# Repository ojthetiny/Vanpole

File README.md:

# Vanpole
tadpole, but van

Layout support

Pic

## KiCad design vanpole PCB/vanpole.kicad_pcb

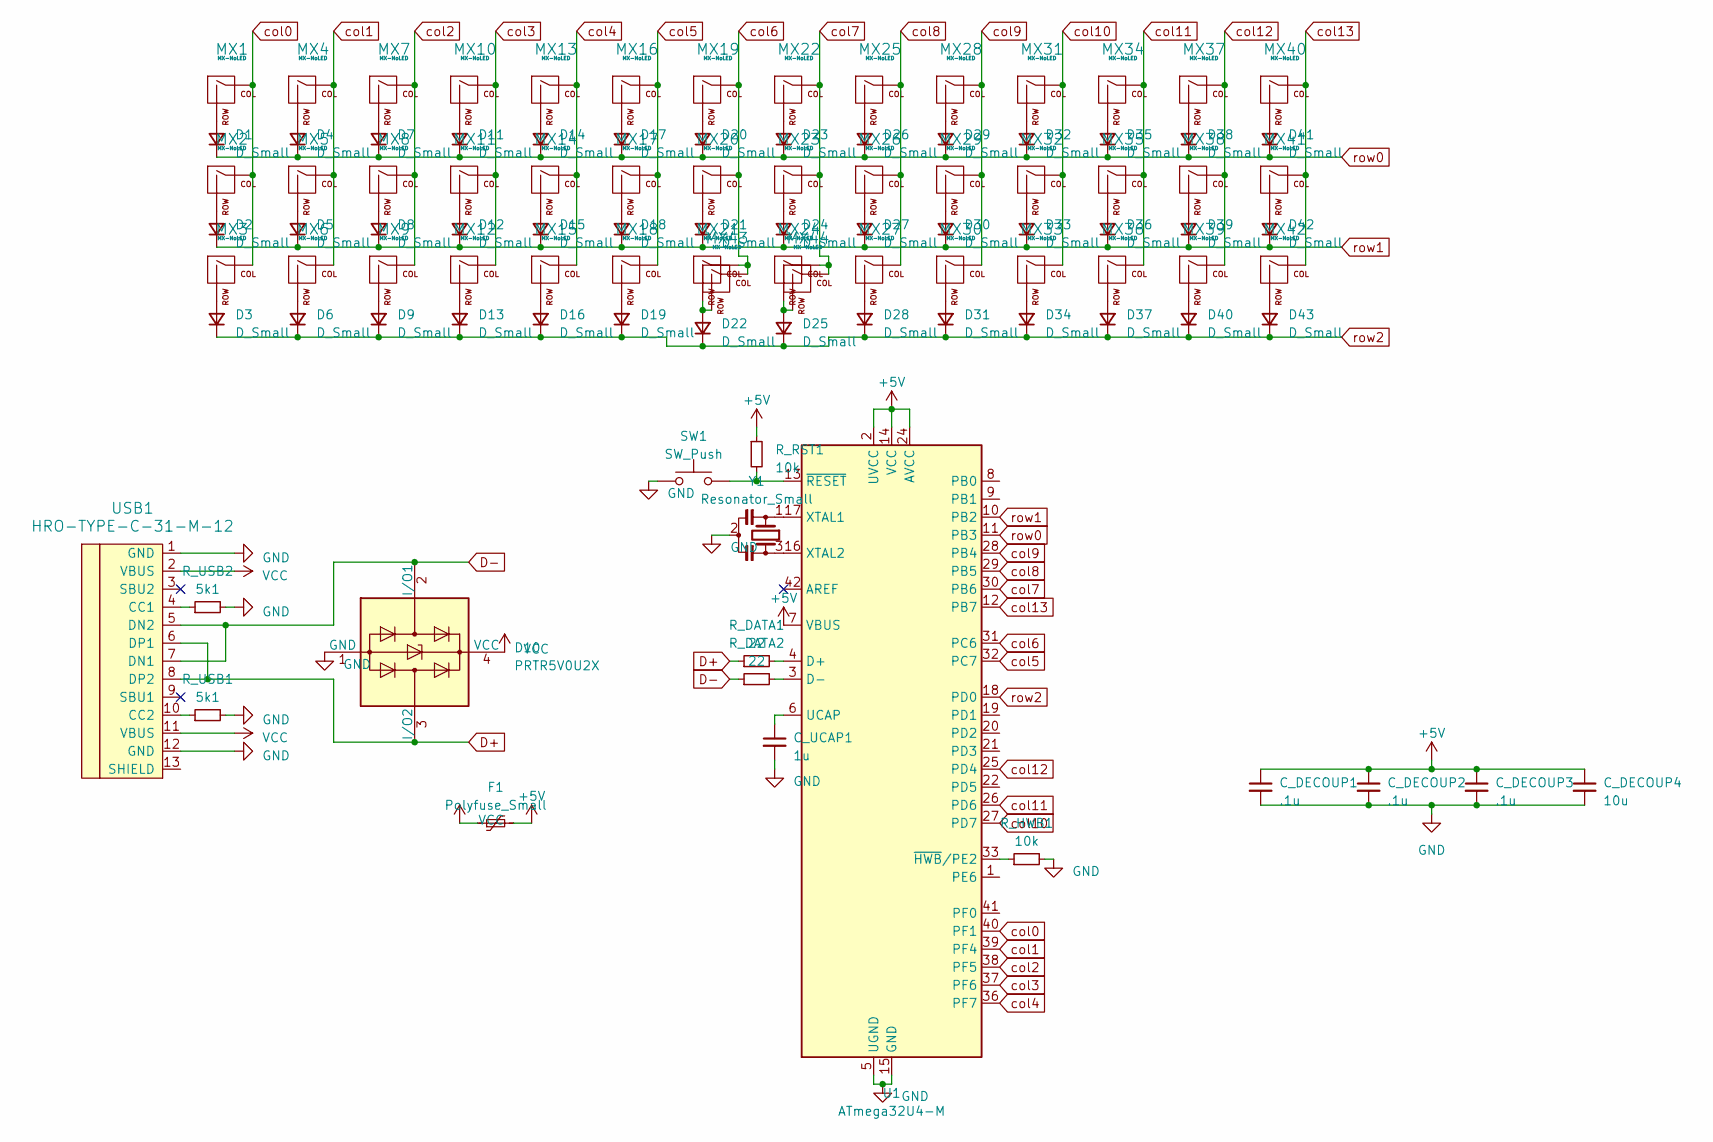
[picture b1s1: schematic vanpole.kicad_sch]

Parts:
C_DECOUP1, C_DECOUP2, C_DECOUP3: .1u; C_0402_1005Metric
C_DECOUP4: 10u; C_0402_1005Metric
C_UCAP1: 1u; C_0402_1005Metric
D1, D2, D3, D4, D5, D6, D7, D8, D9, D11, D12, D13, D14, D15, D16, D17, D18, D19, D20, D21, D22, D23, D24, D25, D26, D27, D28, D29, D30, D31, D32, D33, D34, D35, D36, D37, D38, D39, D40, D41, D42, D43: D_Small; D_SOD-123
D10: PRTR5V0U2X; SOT-143
F1: Polyfuse_Small; Fuse_0805_2012Metric
MX1, MX4, MX5, MX6, MX7, MX8, MX9, MX10, MX11, MX12, MX13, MX14, MX15, MX16, MX17, MX18, MX19, MX20, MX21, MX22, MX23, MX24, MX25, MX26, MX27, MX28, MX29, MX30, MX31, MX32, MX33, MX34, MX35, MX36, MX37, MX38, MX39, MX42: MX-NoLED; MX_1u_NoLED
MX2: MX-NoLED; MX_1.25u_NoLED
MX3, MX40: MX-NoLED; MX_1.75u_NoLED
MX41: MX-NoLED; MX_1.5u_NoLED
MX43, MX44: MX-NoLED; MX_2u_ReversedStabilizers_NoLED
R_DATA1, R_DATA2: 22; R_0402_1005Metric
R_HWB1: 10k; R_0402_1005Metric
R_RST1: 10k; R_0402_1005Metric
R_USB1, R_USB2: 5k1; R_0402_1005Metric
SW1: SW_Push; R_Axial_DIN0204_L3.6mm_D1.6mm_P1.90mm_Vertical
U1: ATmega32U4-M; QFN-44-1EP_7x7mm_P0.5mm_EP5.2x5.2mm
USB1: HRO-TYPE-C-31-M-12; HRO-TYPE-C-31-M-12-Assembly
Y1: Resonator_Small; Resonator_SMD_Murata_CSTxExxV-3Pin_3.0x1.1mm

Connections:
+5V: C_DECOUP1.1, C_DECOUP2.1, C_DECOUP3.1, C_DECOUP4.1, F1.2, R_RST1.1, U1.2 (UVCC), U1.7 (VBUS), U1.14 (VCC), U1.24 (AVCC), U1.34 (VCC), U1.44 (AVCC)
D+: D10.3 (I/O2), R_DATA1.1, USB1.6 (DP1), USB1.8 (DP2)
D-: D10.2 (I/O1), R_DATA2.1, USB1.5 (DN2), USB1.7 (DN1)
GND: C_DECOUP1.2, C_DECOUP2.2, C_DECOUP3.2, C_DECOUP4.2, C_UCAP1.2, D10.1 (GND), R_HWB1.2, R_USB1.2, R_USB2.2, SW1.1, U1.5 (UGND), U1.15 (GND), U1.23 (GND), U1.35 (GND), U1.43 (GND), U1.45 (GND), USB1.1 (GND), USB1.12 (GND), Y1.2
unnamed: C_UCAP1.1, U1.6 (UCAP)
unnamed: D1.2 (A), MX1.2 (ROW)
unnamed: D2.2 (A), MX2.2 (ROW)
unnamed: D3.2 (A), MX3.2 (ROW)
unnamed: D4.2 (A), MX4.2 (ROW)
unnamed: D5.2 (A), MX5.2 (ROW)
unnamed: D6.2 (A), MX6.2 (ROW)
unnamed: D7.2 (A), MX7.2 (ROW)
unnamed: D8.2 (A), MX8.2 (ROW)
unnamed: D9.2 (A), MX9.2 (ROW)
unnamed: D11.2 (A), MX10.2 (ROW)
unnamed: D12.2 (A), MX11.2 (ROW)
unnamed: D13.2 (A), MX12.2 (ROW)
unnamed: D14.2 (A), MX13.2 (ROW)
unnamed: D15.2 (A), MX14.2 (ROW)
unnamed: D16.2 (A), MX15.2 (ROW)
unnamed: D17.2 (A), MX16.2 (ROW)
unnamed: D18.2 (A), MX17.2 (ROW)
unnamed: D19.2 (A), MX18.2 (ROW)
unnamed: D20.2 (A), MX19.2 (ROW)
unnamed: D21.2 (A), MX20.2 (ROW)
unnamed: D22.2 (A), MX21.2 (ROW), MX43.2 (ROW)
unnamed: D23.2 (A), MX22.2 (ROW)
unnamed: D24.2 (A), MX23.2 (ROW)
unnamed: D25.2 (A), MX24.2 (ROW), MX44.2 (ROW)
unnamed: D26.2 (A), MX25.2 (ROW)
unnamed: D27.2 (A), MX26.2 (ROW)
unnamed: D28.2 (A), MX27.2 (ROW)
unnamed: D29.2 (A), MX28.2 (ROW)
unnamed: D30.2 (A), MX29.2 (ROW)
unnamed: D31.2 (A), MX30.2 (ROW)
unnamed: D32.2 (A), MX31.2 (ROW)
unnamed: D33.2 (A), MX32.2 (ROW)
unnamed: D34.2 (A), MX33.2 (ROW)
unnamed: D35.2 (A), MX34.2 (ROW)
unnamed: D36.2 (A), MX35.2 (ROW)
unnamed: D37.2 (A), MX36.2 (ROW)
unnamed: D38.2 (A), MX37.2 (ROW)
unnamed: D39.2 (A), MX38.2 (ROW)
unnamed: D40.2 (A), MX39.2 (ROW)
unnamed: D41.2 (A), MX40.2 (ROW)
unnamed: D42.2 (A), MX41.2 (ROW)
unnamed: D43.2 (A), MX42.2 (ROW)
unnamed: R_DATA1.2, U1.4 (D+)
unnamed: R_DATA2.2, U1.3 (D-)
unnamed: R_HWB1.1, U1.33 (~HWB~/PE2)
unnamed: R_RST1.2, SW1.2, U1.13 (~RESET)
unnamed: R_USB2.1, USB1.4 (CC1)
unnamed: U1.16 (XTAL2), Y1.3
unnamed: U1.17 (XTAL1), Y1.1
unnamed: R_USB1.1, USB1.10 (CC2)
VCC: D10.4 (VCC), F1.1, USB1.2 (VBUS), USB1.11 (VBUS)
col0: MX1.1 (COL), MX2.1 (COL), MX3.1 (COL), U1.40 (PF1)
col1: MX4.1 (COL), MX5.1 (COL), MX6.1 (COL), U1.39 (PF4)
col2: MX7.1 (COL), MX8.1 (COL), MX9.1 (COL), U1.38 (PF5)
col3: MX10.1 (COL), MX11.1 (COL), MX12.1 (COL), U1.37 (PF6)
col4: MX13.1 (COL), MX14.1 (COL), MX15.1 (COL), U1.36 (PF7)
col5: MX16.1 (COL), MX17.1 (COL), MX18.1 (COL), U1.32 (PC7)
col6: MX19.1 (COL), MX20.1 (COL), MX21.1 (COL), MX43.1 (COL), U1.31 (PC6)
col7: MX22.1 (COL), MX23.1 (COL), MX24.1 (COL), MX44.1 (COL), U1.30 (PB6)
col8: MX25.1 (COL), MX26.1 (COL), MX27.1 (COL), U1.29 (PB5)
col9: MX28.1 (COL), MX29.1 (COL), MX30.1 (COL), U1.28 (PB4)
col10: MX31.1 (COL), MX32.1 (COL), MX33.1 (COL), U1.27 (PD7)
col11: MX34.1 (COL), MX35.1 (COL), MX36.1 (COL), U1.26 (PD6)
col12: MX37.1 (COL), MX38.1 (COL), MX39.1 (COL), U1.25 (PD4)
col13: MX40.1 (COL), MX41.1 (COL), MX42.1 (COL), U1.12 (PB7)
row0: D1.1 (K), D4.1 (K), D7.1 (K), D11.1 (K), D14.1 (K), D17.1 (K), D20.1 (K), D23.1 (K), D26.1 (K), D29.1 (K), D32.1 (K), D35.1 (K), D38.1 (K), D41.1 (K), U1.11 (PB3)
row1: D2.1 (K), D5.1 (K), D8.1 (K), D12.1 (K), D15.1 (K), D18.1 (K), D21.1 (K), D24.1 (K), D27.1 (K), D30.1 (K), D33.1 (K), D36.1 (K), D39.1 (K), D42.1 (K), U1.10 (PB2)
row2: D3.1 (K), D6.1 (K), D9.1 (K), D13.1 (K), D16.1 (K), D19.1 (K), D22.1 (K), D25.1 (K), D28.1 (K), D31.1 (K), D34.1 (K), D37.1 (K), D40.1 (K), D43.1 (K), U1.18 (PD0)

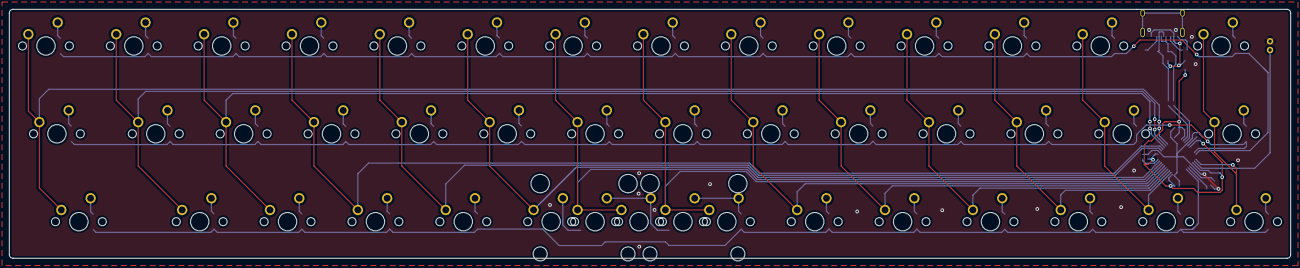
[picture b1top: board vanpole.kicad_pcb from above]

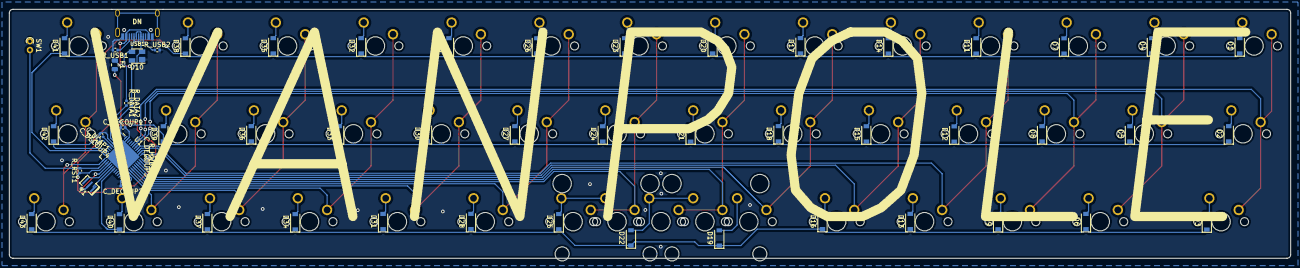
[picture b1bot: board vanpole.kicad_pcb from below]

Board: 2 copper layers, 277.8 x 54.0 mm, 103 parts (59 on the bottom side), 73 nets.

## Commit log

2022-03-13 add images
2022-03-13 rename kle pic
